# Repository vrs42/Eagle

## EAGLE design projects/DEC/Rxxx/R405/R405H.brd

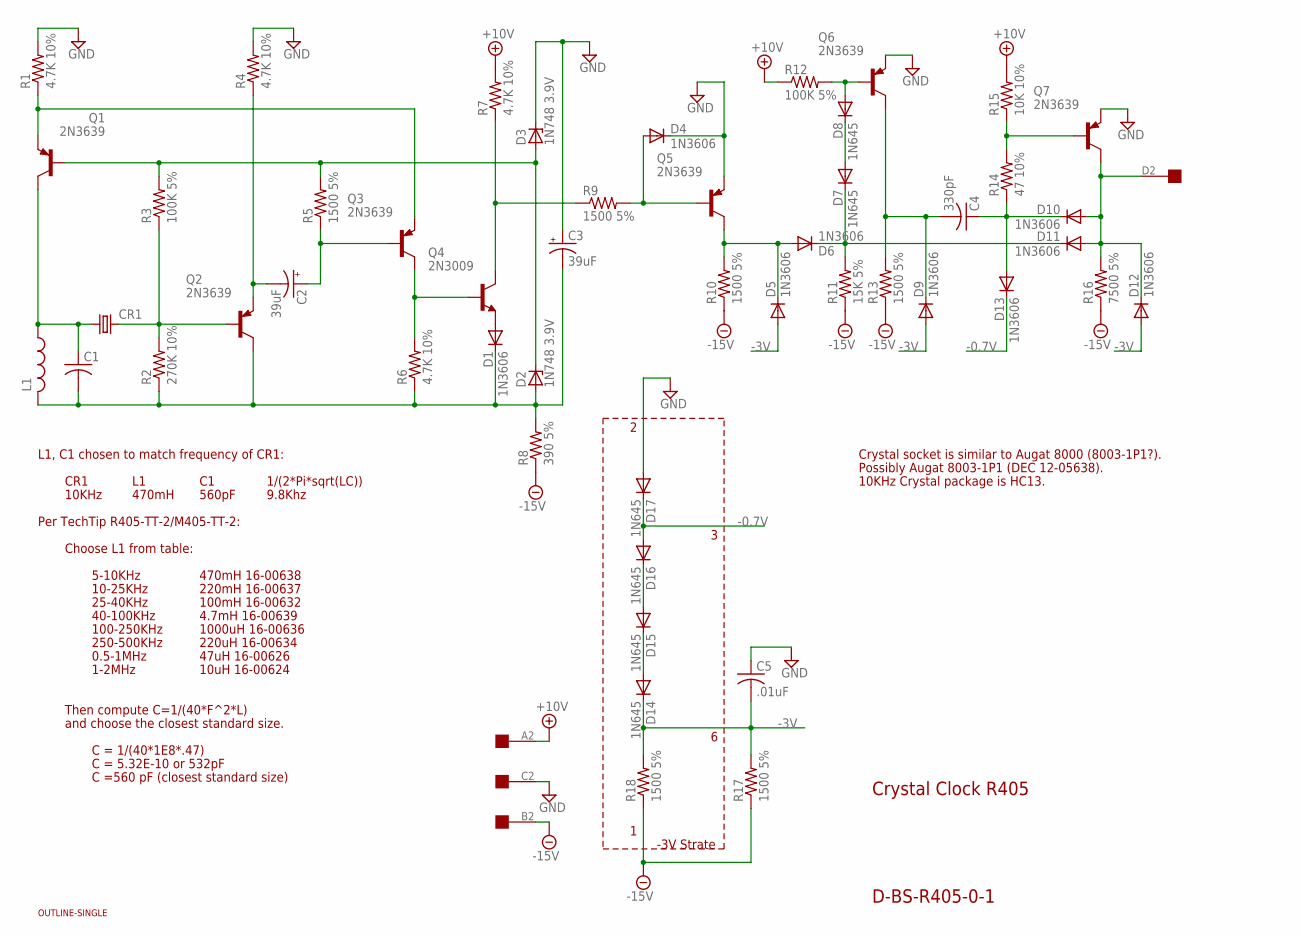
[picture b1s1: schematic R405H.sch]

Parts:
C1: C-US150-054X183; C150-054X183
C2, C3: 39uF; E15-5
C4: 330pF; C150-054X183
C5: .01uF; C150-054X183
CR1: CRYSTALHC13U-H; HC13U-H
D1, D4, D5, D6, D9, D10, D11, D12, D13: 1N3606; DO35-10
D2, D3: 1N748 3.9V; DO35Z10
D7, D8, D14, D15, D16, D17: 1N645; DO35-10
L1: L-US0207/7; 0207/7
Q1, Q2, Q3, Q5, Q6, Q7: 2N3639; TO39
Q4: 2N3009; TO5
R1, R4, R6, R7: 4.7K 10%; 0207/10
R2: 270K 10%; 0207/10
R3, R12: 100K 5%; 0207/10
R5, R9, R10, R13, R17, R18: 1500 5%; 0207/10
R8: 390 5%; 0207/10
R11: 15K 5%; 0207/10
R14: 47 10%; 0207/10
R15: 10K 10%; 0207/10
R16: 7500 5%; 0207/10
U$1: OUTLINE-SINGLE; SINGLE
U$2: EDGE-1; EDGE-CON1

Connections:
+10V: R7.2, R12.1, R15.2, U$2.A2
-0.7V: D13.C, D16.A, D17.C
-3V: C5.2, D5.A, D9.A, D12.A, D14.C, R17.2, R18.2
-15V: R8.1, R10.1, R11.1, R13.1, R16.1, R17.1, R18.1, U$2.B2
GND: C3.+, C5.1, D3.C, D4.C, D17.A, Q5.1 (E), Q6.1 (E), Q7.1 (E), R1.2, R4.2, U$2.C2
unnamed: Q1.1 (E), Q3.1 (E), R1.1
unnamed: C1.1, CR1.1, L1.1, Q1.3 (C)
unnamed: C1.2, C3.-, D1.C, D2.A, L1.2, Q2.3 (C), R2.1, R6.1, R8.2
unnamed: C2.-, Q2.1 (E), R4.1
unnamed: D1.A, Q4.1 (E)
unnamed: CR1.2, Q2.2 (B), R2.2, R3.1
unnamed: D2.C, D3.A, Q1.2 (B), R3.2, R5.2
unnamed: D15.A, D16.C
unnamed: D14.A, D15.C
unnamed: C2.+, Q3.2 (B), R5.1
unnamed: Q3.3 (C), Q4.2 (B), R6.2
unnamed: Q4.3 (C), R7.1, R9.1
unnamed: D4.A, Q5.2 (B), R9.2
unnamed: D5.C, D6.A, Q5.3 (C), R10.2
unnamed: D8.A, Q6.2 (B), R12.2
unnamed: D7.A, D8.C
unnamed: D6.C, D7.C, D11.C, R11.2
unnamed: C4.2, D9.C, Q6.3 (C), R13.2
unnamed: C4.1, D10.C, D13.A, R14.1
unnamed: Q7.2 (B), R14.2, R15.1
unnamed: D10.A, D11.A, D12.C, Q7.3 (C), R16.2, U$2.D2

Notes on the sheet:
Crystal Clock R405
D-BS-R405-0-1
-3V Strate
10KHz
CR1
470mH
560pF
1/(2*Pi*sqrt(LC))
9.8Khz
Possibly Augat 8003-1P1 (DEC 12-05638).
10KHz Crystal package is HC13.
L1, C1 chosen to match frequency of CR1:
Crystal socket is similar to Augat 8000 (8003-1P1?).
Per TechTip R405-TT-2/M405-TT-2:
Choose L1 from table:
5-10KHz
10-25KHz
25-40KHz
40-100KHz
100-250KHz
250-500KHz
0.5-1MHz
1-2MHz
10uH 16-00624
47uH 16-00626
470mH 16-00638
220mH 16-00637
100mH 16-00632
4.7mH 16-00639
1000uH 16-00636
220uH 16-00634
Then compute C=1/(40*F^2*L)
and choose the closest standard size.
C = 1/(40*1E8*.47)
C = 5.32E-10 or 532pF
C =560 pF (closest standard size)

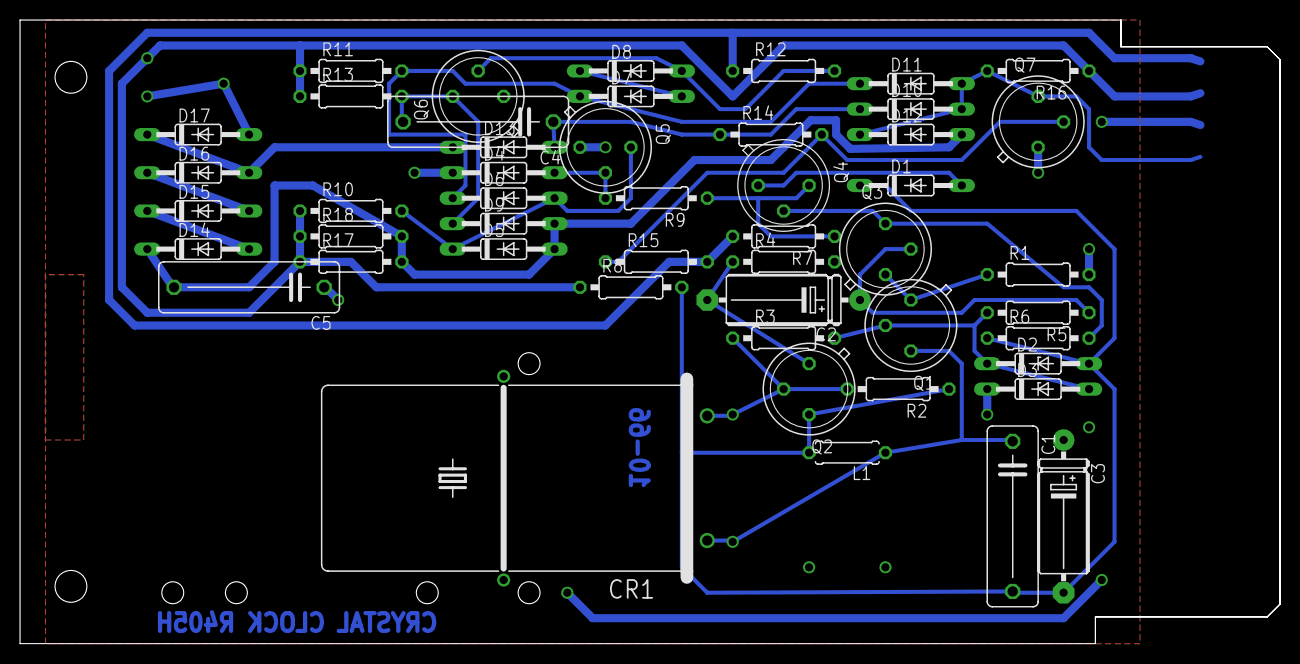
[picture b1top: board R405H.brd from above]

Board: 2 copper layers, 125.7 x 62.2 mm, 51 parts (0 on the bottom side), 26 nets.

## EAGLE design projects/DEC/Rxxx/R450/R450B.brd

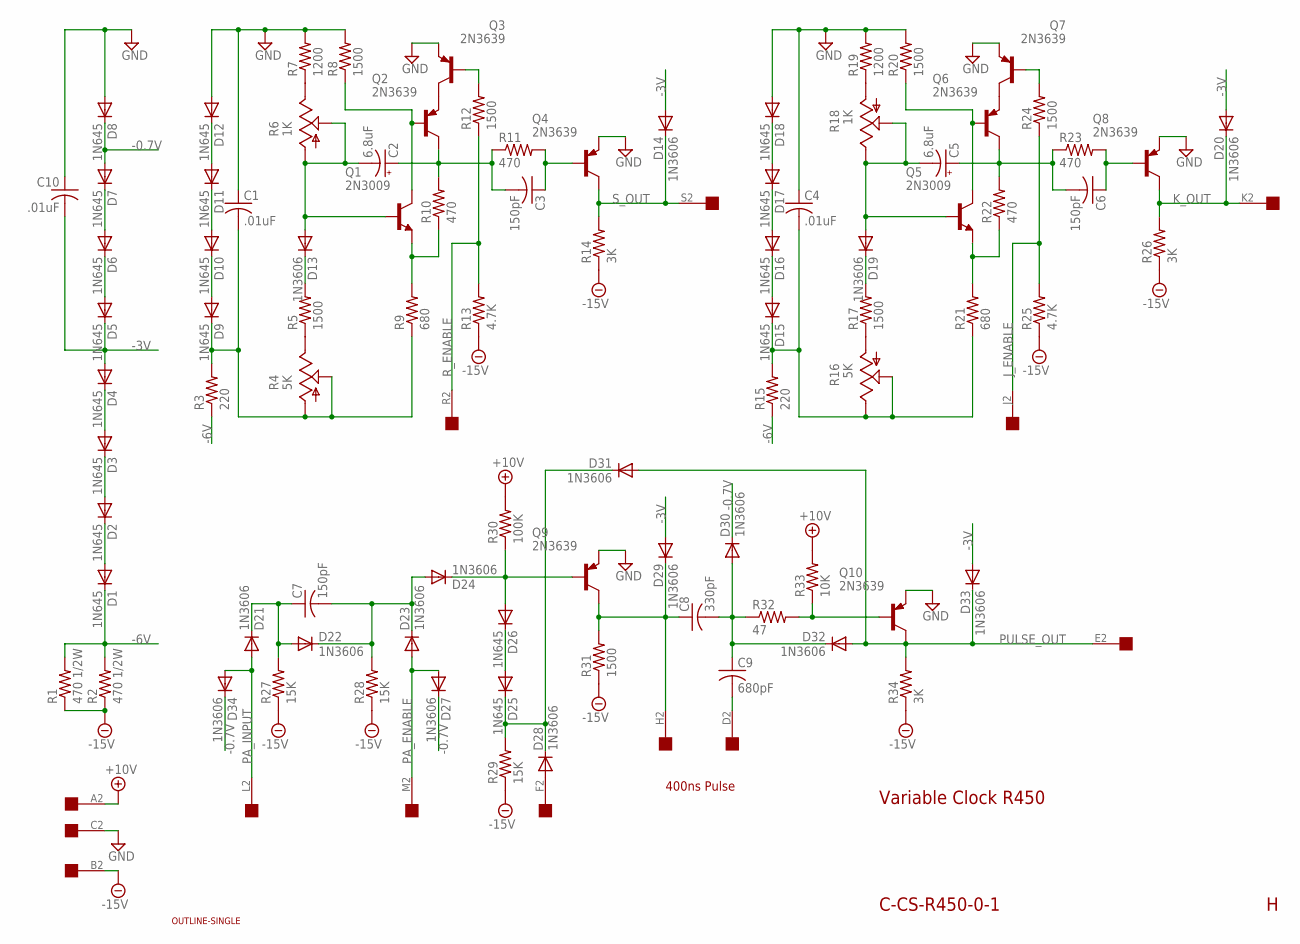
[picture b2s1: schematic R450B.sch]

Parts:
C1, C4, C10: .01uF; C063-025X075
C2, C5: 6.8uF; E15-5
C3: 150pF; C075-032X103
C6, C7: 150pF; C063-025X075
C8: 330pF; C063-025X075
C9: 680pF; C063-025X075
D1, D2, D3, D4, D5, D6, D7, D8, D9, D10, D11, D12, D15, D16, D17, D18, D25, D26: 1N645; DO35-10
D13, D14, D19, D20, D21, D22, D23, D24, D27, D28, D29, D30, D31, D32, D33, D34: 1N3606; DO35-10
Q1, Q5: 2N3009; TO5
Q2, Q3, Q4, Q6, Q7, Q8, Q9, Q10: 2N3639; TO39
R1, R2: 470 1/2W; 0411/15
R3, R15: 220; 0207/10
R4, R16: 5K; CT6
R5, R8, R12, R17, R20, R24, R31: 1500; 0207/10
R6, R18: 1K; CT6
R7, R19: 1200; 0207/10
R9, R21: 680; 0207/10
R10, R11, R22, R23: 470; 0207/10
R13, R25: 4.7K; 0207/10
R14, R26, R34: 3K; 0207/10
R27, R28, R29: 15K; 0207/10
R30: 100K; 0207/10
R32: 47; 0207/10
R33: 10K; 0207/10
U$1: OUTLINE-SINGLE; SINGLE
U$2: EDGE-1; EDGE-CON1

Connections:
+10V: R30.2, R33.2, U$2.A2
-0.7V: D7.A, D8.C, D27.C, D30.C, D34.C
-3V: C10.2, D4.A, D5.C, D14.A, D20.A, D29.A, D33.A
-6V: D1.C, R1.2, R2.2, R3.1, R15.1
-15V: R1.1, R2.1, R13.1, R14.1, R25.1, R26.1, R27.1, R28.1, R29.1, R31.1, R34.1, U$2.B2
GND: C1.1, C4.1, C10.1, D8.A, D12.A, D18.A, Q3.1 (E), Q4.1 (E), Q7.1 (E), Q8.1 (E), Q9.1 (E), Q10.1 (E), R7.2, R8.2, R19.2, R20.2, U$2.C2
J_ENABLE: R24.1, R25.2, U$2.J2
K_OUT: D20.C, Q8.3 (C), R26.2, U$2.K2
unnamed: D1.A, D2.C
unnamed: D5.A, D6.C
unnamed: D11.A, D12.C
unnamed: D10.A, D11.C
unnamed: D9.A, D10.C
unnamed: C1.2, D9.C, R3.2, R4.A, R4.S, R9.1
unnamed: Q1.1 (E), R9.2, R10.1
unnamed: R4.E, R5.1
unnamed: D13.C, R5.2
unnamed: C2.-, D13.A, Q1.2 (B), R6.A, R6.S
unnamed: Q1.3 (C), Q2.2 (B), R8.1
unnamed: C2.+, C3.2, Q2.3 (C), R10.2, R11.1
unnamed: D2.A, D3.C
unnamed: D3.A, D4.C
unnamed: Q3.2 (B), R12.2
unnamed: Q2.1 (E), Q3.3 (C)
unnamed: R6.E, R7.1
unnamed: C3.1, Q4.2 (B), R11.2
unnamed: D17.A, D18.C
unnamed: D16.A, D17.C
unnamed: D15.A, D16.C
unnamed: C4.2, D15.C, R15.2, R16.E, R16.S, R21.1
unnamed: D19.C, R17.2
unnamed: D28.A, U$2.F2
unnamed: Q5.1 (E), R21.2, R22.1
unnamed: C7.1, D21.C, D22.A, R27.2
unnamed: R18.A, R19.1
unnamed: C7.2, D22.C, D23.C, D24.A, R28.2
unnamed: Q5.3 (C), Q6.2 (B), R20.1
unnamed: Q6.1 (E), Q7.3 (C)
unnamed: R16.A, R17.1
unnamed: C5.-, D19.A, Q5.2 (B), R18.E, R18.S
unnamed: C5.+, C6.2, Q6.3 (C), R22.2, R23.1
unnamed: C6.1, Q8.2 (B), R23.2
unnamed: Q7.2 (B), R24.2
unnamed: C8.1, D29.C, Q9.3 (C), R31.2, U$2.H2
unnamed: D24.C, D26.A, Q9.2 (B), R30.1
unnamed: D25.A, D26.C
unnamed: D25.C, D28.C, D31.C, R29.2
unnamed: C8.2, C9.1, D30.A, D32.C, R32.1
unnamed: C9.2, U$2.D2
unnamed: Q10.2 (B), R32.2, R33.1
unnamed: D6.A, D7.C
PA_ENABLE: D23.A, D27.A, U$2.M2
PA_INPUT: D21.A, D34.A, U$2.L2
PULSE_OUT: D31.A, D32.A, D33.C, Q10.3 (C), R34.2, U$2.E2
R_ENABLE: R12.1, R13.2, U$2.R2
S_OUT: D14.C, Q4.3 (C), R14.2, U$2.S2

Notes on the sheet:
Variable Clock R450
C-CS-R450-0-1
400ns Pulse

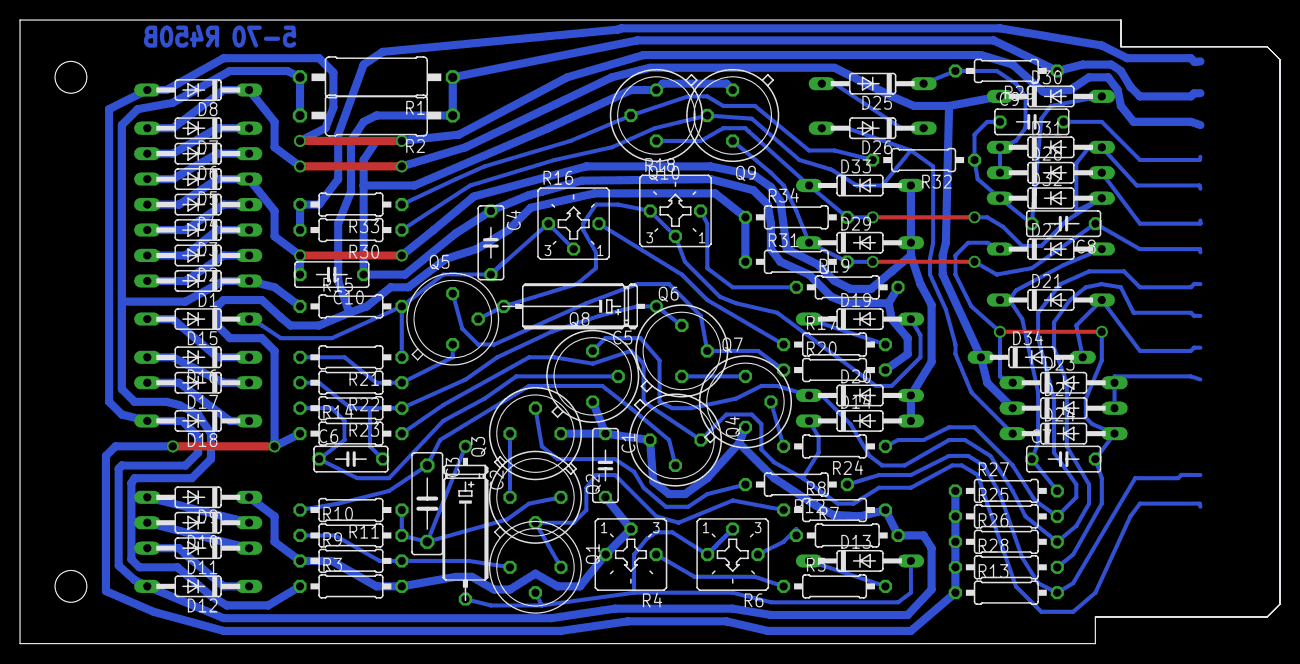
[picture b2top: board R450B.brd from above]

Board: 2 copper layers, 125.7 x 62.2 mm, 90 parts (0 on the bottom side), 56 nets.
